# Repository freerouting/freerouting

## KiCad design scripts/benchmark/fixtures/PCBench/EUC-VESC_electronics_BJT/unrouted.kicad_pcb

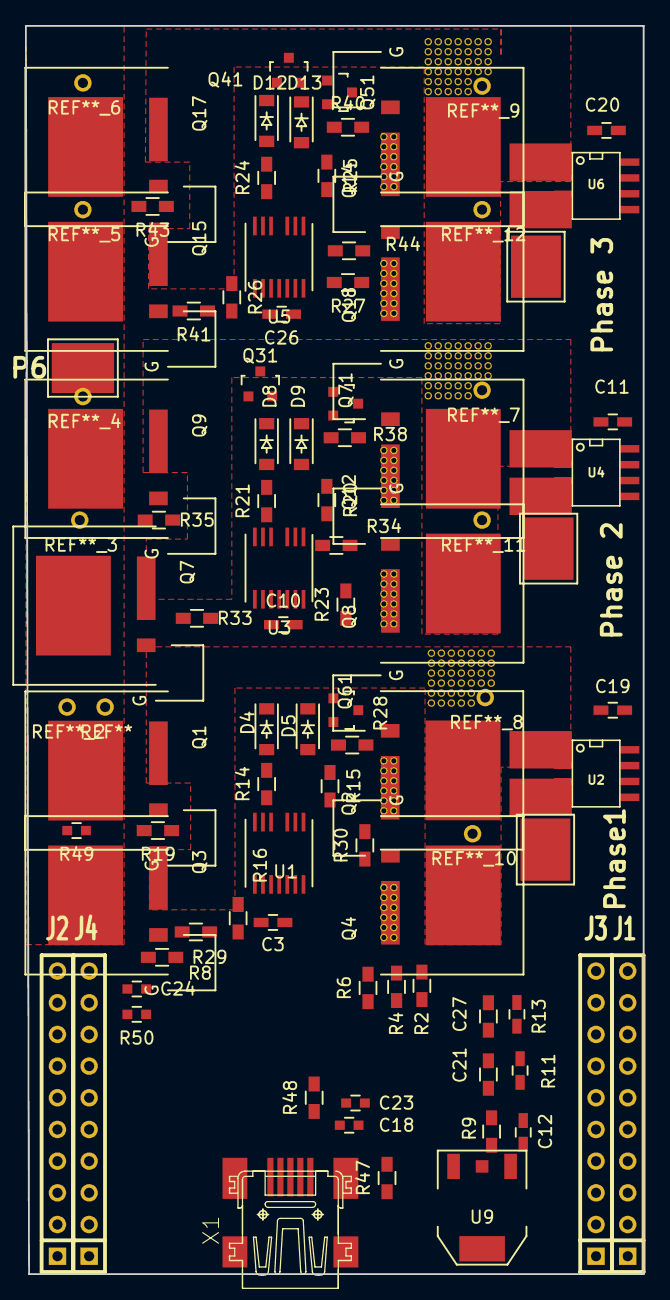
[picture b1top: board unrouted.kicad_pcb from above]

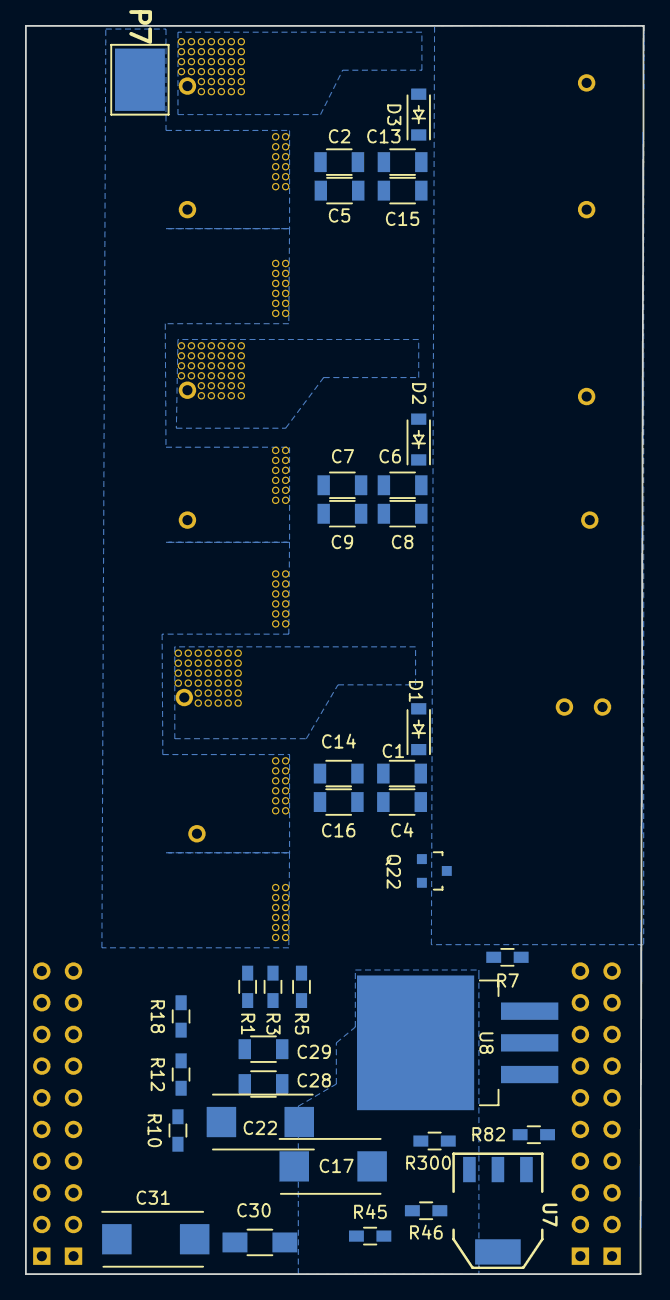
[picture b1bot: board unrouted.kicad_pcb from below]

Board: 4 copper layers, 49.5 x 100.1 mm, 120 parts (36 on the bottom side), 68 nets, no tracks yet.

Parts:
C1, C2, C6, C7, C13, C14: 0.1uf; C_1206
C3, C10, C11, C12, C19, C20, C21, C26, C27: 0.1uf; C_0603_HandSoldering
C4, C5, C8, C9, C15, C16, C28, C29: 10uf; C_1206
C17, C22, C31: 100uf; TantalC_SizeD_EIA-7343_Reflow
C18, C23, C24: 10uf; C_0603
C30: 2.2uf; C_1206_HandSoldering
D1, D2, D3: DFLS1150-7; SOD-123
D4, D5, D8, D9, D12, D13: D_Schottky_Small; SOD-123
J1: Ti_Booster_40_J1; SIL-10J1
J2: Ti_Booster_40_J2; SIL-10J2
J3: Ti_Booster_40_J3; SIL-10J3
J4: Ti_Booster_40_J4; SIL-10J4
P6: IN+; 1PAD_4x5mm
P7: IN-; 1PAD_4x5mm
Phase1: MOTOR3; 1PAD_4x5mm
Phase 2: MOTOR2; 1PAD_4x5mm
Phase 3: MOTOR1; 1PAD_4x5mm
Q1, Q2, Q3, Q4, Q7, Q8, Q9, Q12, Q14, Q15, Q17, Q18: FDMT-800; PQFN-8L-FET
Q22, Q31, Q41, Q51, Q61, Q71: BC807-40; SOT-23
R1, R3, R5, R7: 1.3K; R_0603_HandSoldering
R2, R4, R6, R8: 39K; R_0603_HandSoldering
R9, R11, R13: 2k; R_0603_HandSoldering
R10, R12, R18: 3.9k; R_0603_HandSoldering
R14, R15, R20, R21, R24, R25: 10R; R_0603_HandSoldering
R16, R23, R26, R27: 39k; R_0603_HandSoldering
R19, R28, R29, R30, R33, R34, R35, R38, R40, R41, R43, R44, R45, R46: R22; R_0603_HandSoldering
R47: R0; R_0603_HandSoldering
R48: r0; R_0603_HandSoldering
R49: NTC10K; C_0603
R50: 10K; C_0603
R82: R; R_0603_HandSoldering
R300: R_Small; R_0603_HandSoldering
U1, U3, U5: ADuM7223; LGA-13
U2, U4, U6: ACS723; ACS723_40
U7: NCP1117ST33T3G; SOT-223
U8: tl783; TO-263-3Lead
U9: LM340MPX-5; SOT-223
X1: MINI-USB-SCHIELD-32005-201; con-cypressindustries-32005-201

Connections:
+3V3: C30.1, C31.1, J1.1, R49.1, U7.2
+5V: C3.2, C10.2, C11.1, C17.1, C18.1, C19.2, C20.1, C23.1, C26.1, J3.1, R47.2, U1.7, U2.8, U3.7, U4.8, U5.7, U6.8, U7.3, U9.3
/Power MOSFETS/CurrentA: C12.1, J3.7, R9.2, R10.1
/Power MOSFETS/CurrentB: C21.1, J3.8, R11.2, R12.1
/Power MOSFETS/CurrentC: C27.1, J3.9, R13.2, R18.1
/Power MOSFETS/H1_VS: C1.2, C4.2, Q1.2, Q2.1, Q3.2, Q4.1, Q22.3, R2.2, R16.1, U1.11, U2.1, U2.2
/Power MOSFETS/H2_VS: C6.2, C8.2, Q7.2, Q8.1, Q9.2, Q12.1, Q31.3, R4.2, U3.11, U4.1, U4.2
/Power MOSFETS/H3_VS: C13.2, C15.2, Q14.1, Q15.2, Q17.2, Q18.1, Q41.3, R6.2, R26.1, U5.11, U6.1, U6.2
/Power MOSFETS/M_H1: J4.1, U1.2
/Power MOSFETS/M_H2: J4.3, U3.2
/Power MOSFETS/M_H3: J4.5, U5.2
/Power MOSFETS/M_L1: J4.2, U1.3
/Power MOSFETS/M_L2: J4.4, U3.3
/Power MOSFETS/M_L3: J4.6, U5.3
/Power MOSFETS/PHASE_1: Phase1.1, U2.3, U2.4
/Power MOSFETS/PHASE_2: Phase 2.1, U4.3, U4.4
/Power MOSFETS/PHASE_3: Phase 3.1, U6.3, U6.4
GND: C2.2, C3.1, C5.2, C7.2, C9.2, C10.1, C11.2, C12.2, C14.2, C16.2, C17.2, C18.2, C19.1, C20.2, C21.2, C22.2, C23.2, C24.1, C26.2, C27.2, C28.1, C29.1, C30.2, C31.2, J2.1, J3.2, P7.1, Q2.2, Q4.2, Q8.2, Q12.2, Q14.2, Q18.2, Q51.3, Q61.3, Q71.3, R1.1, R3.1, R5.1, R7.1, R10.2, R12.2, R18.2, R23.1, R27.1, R48.1, R50.1, R300.2, U1.1, U1.5, U1.8, U2.5, U3.1, U3.5, U3.8, U4.5, U5.1, U5.5, U5.8, U6.5, U7.1, U9.2, U9.4
unnamed: C1.1, C4.1, D1.1, U1.13
unnamed: C6.1, C8.1, D2.1, U3.13
unnamed: C13.1, C15.1, D3.1, U5.13
unnamed: C24.2, J2.10, R49.2, R50.2
unnamed: D4.1, Q22.2, R16.2, R19.1, R29.1
unnamed: D4.2, Q22.1, R14.2
unnamed: D5.1, Q61.2, R28.2, R30.2
unnamed: D5.2, Q61.1, R15.1
unnamed: D8.1, Q31.2, R33.1, R35.1
unnamed: D8.2, Q31.1, R21.2
unnamed: D9.1, Q71.2, R34.1, R38.1
unnamed: D9.2, Q71.1, R20.1
unnamed: D12.1, Q41.2, R26.2, R41.1, R43.1
unnamed: D12.2, Q41.1, R24.2
unnamed: D13.1, Q51.2, R40.1, R44.1
unnamed: D13.2, Q51.1, R25.1
unnamed: J2.2, J2.3, R45.2
unnamed: J2.4, J2.5, R46.1
unnamed: J3.3, R7.2, R8.1
unnamed: J3.4, R1.2, R2.1
unnamed: J3.5, R3.2, R4.1
unnamed: J3.6, R5.2, R6.1
unnamed: Q1.3, R19.2
unnamed: Q2.3, R28.1
unnamed: Q3.3, R29.2
unnamed: Q4.3, R30.1
unnamed: Q7.3, R33.2
unnamed: Q8.3, R34.2
unnamed: Q9.3, R35.2
unnamed: Q12.3, R38.2
unnamed: Q14.3, R40.2
unnamed: Q15.3, R41.2
unnamed: Q17.3, R43.2
unnamed: Q18.3, R44.2
unnamed: R9.1, U2.7
unnamed: R11.1, U4.7
unnamed: R13.1, U6.7
unnamed: R14.1, U1.12
unnamed: R15.2, U1.9
unnamed: R20.2, U3.9
unnamed: R21.1, U3.12
unnamed: R24.1, U5.12
unnamed: R25.2, U5.9
unnamed: R45.1, X1.3
unnamed: R46.2, X1.2
unnamed: R47.1, X1.5
unnamed: R48.2, X1.1
unnamed: R82.2, R300.1, U8.1
VDD: C2.1, C5.1, C7.1, C9.1, C14.1, C16.1, C22.1, C28.2, C29.2, D1.2, D2.2, D3.2, R82.1, U3.10, U5.10, U8.2, U8.4, U9.1
V_SUPPLY: P6.1, Q1.1, Q3.1, Q7.1, Q9.1, Q15.1, Q17.1, R8.2, U8.3

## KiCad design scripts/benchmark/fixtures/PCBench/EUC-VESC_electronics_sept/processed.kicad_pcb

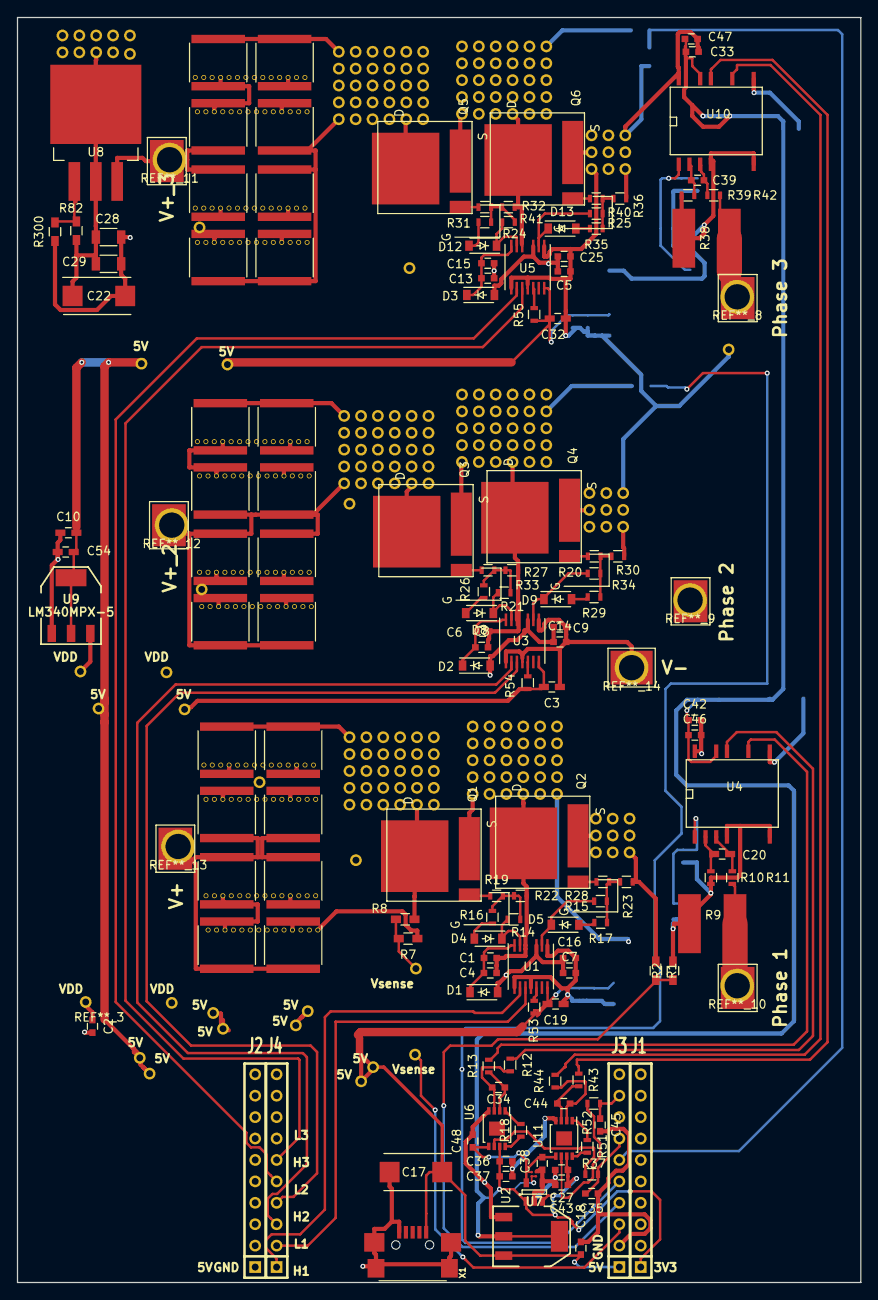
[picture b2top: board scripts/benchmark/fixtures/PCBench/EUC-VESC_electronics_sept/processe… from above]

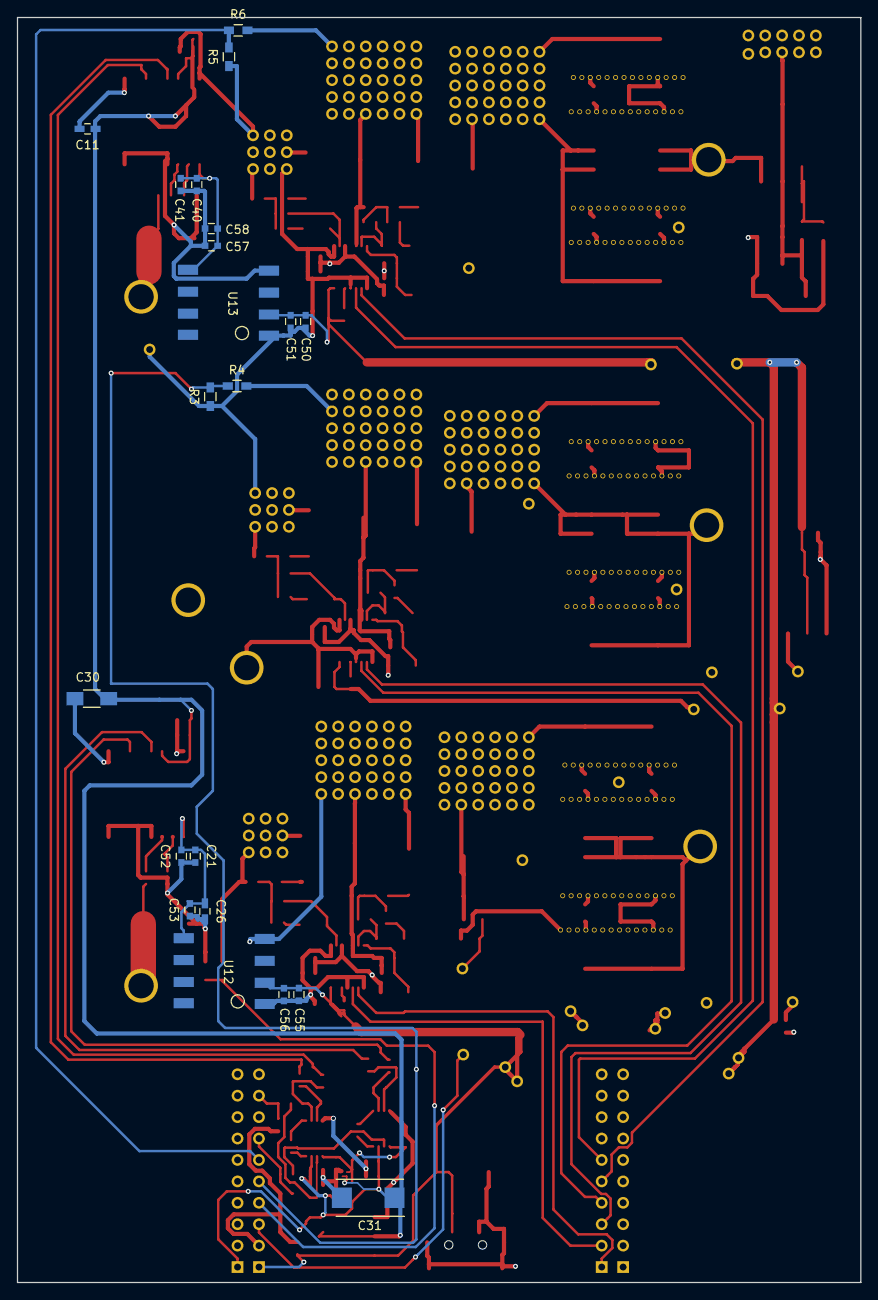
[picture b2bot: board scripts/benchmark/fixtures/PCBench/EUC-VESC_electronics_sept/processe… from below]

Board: 4 copper layers, 100.0 x 150.0 mm, 169 parts (21 on the bottom side), 74 nets.

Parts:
C1, C2, C6, C7, C13, C14, C25, C33, C36, C38, C41, C43, C46, C48, C50, C53, C55, C58: 0.1uf; C_0603
C3, C10, C19, C26, C32: 0.1uf; C_0603_HandSoldering
C4, C16: 2.2uf; C_0603
C5, C8, C9, C15: 2.2; C_0603
C11: 1uf; C_0603_HandSoldering
C17, C22, C31: 100uf; TantalC_SizeD_EIA-7343_Reflow
C18, C21, C27, C37, C40, C42, C47, C51, C52, C56, C57: 10uf; C_0603
C20: 33nf; C_0603_HandSoldering
C28, C29: 10uf; C_1206
C30: 2.2uf; C_1206_HandSoldering
C34, C44: 4.7nf; C_0603
C35, C45: 100pf; C_0603
C39: 33nf; C_0603
C49, C49_2, C49_3, C49_4, C49_5, C49_6, C49_7, C49_8, C49_9, C49_10, C49_11, C49_12, C49_13, C49_14, C49_15, C49_16, C49_17, C49_18, C49_19, C49_20, C49_21, C49_22, C49_23, C49_24: 15uf; C_2225_invis
C54: 10uf; C_0603_HandSoldering
D1, D2, D3: DFLS1150-7; SOD-123
D4, D5, D8, D9, D12, D13: D_Schottky_Small; SOD-123
J1: Ti_Booster_40_J1; SIL-10J1
J2: Ti_Booster_40_J2; SIL-10J2
J3: Ti_Booster_40_J3; SIL-10J3
J4: Ti_Booster_40_J4; SIL-10J4
Phase 1: MOTOR3; 1PAD_4x5mm
Phase 2: MOTOR2; 1PAD_4x5mm
Phase 3: MOTOR1; 1PAD_4x5mm
Q1, Q2, Q3, Q4, Q5, Q6: FDMT-800; P-PG-HSOF-08
R1, R3, R5, R7: 1.3K; R_0603_HandSoldering
R2, R4, R6, R8: 39K; R_0603_HandSoldering
R9, R38: 0.001R; shunt_ERJ-MS6SF1M0U
R10, R11, R37, R39, R42, R52: 20R; R_0603
R12, R13, R43, R44: R20; R_0603
R14, R15, R20, R21, R24, R25: 10R; R_0603
R16, R17, R26, R29, R31, R35: R4; R_0603
R18, R51: 10Mr; R_0603
R19, R28, R33, R34, R40, R41: ferrite; R_0603
R22, R23, R27, R30, R32, R36: R39k; R_0603
R53, R54, R55: r20; R_0603
R82: R; R_0603_HandSoldering
R300: R_Small; R_0603_HandSoldering
U1, U3, U5: ADuM7223; LGA-13
U2: TPS72116DBVR; SOT-23-5
U4, U10: SI8920; SI_8920SO-16
U6, U11: ad623; MSOP-8-1EP_3x3mm_Pitch0.65mm
U7: NCP1117ST33T3G; SOT-223
U8: tl783; TO-263-3Lead
U9: LM340MPX-5; SOT223_bcp53
U12, U13: R1SE-0505-R; recom_power
V+: IN+; 1PAD_4x5mm
V+_2, V+_3: IN+; 1PAD_4x5mm
V-: IN-; 1PAD_4x5mm
X1: MINI-USB-SCHIELD-32005-201; USB-UX60R-MB-5ST

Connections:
+1V5: C38.1, C48.1, U2.5, U6.5, U11.5
+3V3: C11.1, C27.1, C30.1, C31.1, C33.1, C36.1, C37.1, C42.1, C43.1, C46.1, C47.1, J1.1, U2.1, U2.3, U4.8, U6.7, U7.2, U10.8, U11.7
+5V: C3.2, C10.2, C17.1, C18.1, C19.2, C32.1, C50.2, C51.2, C54.1, C55.2, C56.2, J3.1, R53.2, R54.2, R55.2, U1.7, U3.7, U5.7, U7.3, U9.3, U12.2, U13.2, X1.1
+5VA: C21.1, C26.1, C52.2, C53.2, U4.1, U12.5
+5VD: C40.1, C41.1, C57.2, C58.2, U10.1, U13.5
/Power MOSFETS/CurrentA: C35.1, J3.7, R37.1
/Power MOSFETS/CurrentC: C45.1, J3.9, R52.1
/Power MOSFETS/H2_VS: C6.2, C8.2, Phase 2.1, Q3.2, Q4.1, R4.2, R27.1, U3.11
/Power MOSFETS/M_H1: J4.1, U1.2
/Power MOSFETS/M_H2: J4.3, U3.2
/Power MOSFETS/M_H3: J4.5, U5.2
/Power MOSFETS/M_L1: J4.2, U1.3
/Power MOSFETS/M_L2: J4.4, U3.3
/Power MOSFETS/M_L3: J4.6, U5.3
/Power MOSFETS/PHASE_1: Phase 1.1, R9.1, R11.2
/Power MOSFETS/PHASE_3: Phase 3.1, R38.1, R42.2
/Power MOSFETS/sense1_N: R13.2, U4.6
/Power MOSFETS/sense1_P: R12.2, U4.7
/Power MOSFETS/sense2_N: R44.2, U10.6
/Power MOSFETS/sense2_P: R43.2, U10.7
GND: C2.2, C3.1, C5.2, C7.2, C9.2, C10.1, C11.2, C14.2, C16.2, C17.2, C18.2, C19.1, C22.2, C25.2, C27.2, C28.1, C29.1, C30.2, C31.2, C32.2, C33.2, C35.2, C36.2, C37.2, C38.2, C42.2, C43.2, C45.2, C46.2, C47.2, C48.2, C49.2, C49_2.2, C49_3.2, C49_4.2, C49_5.2, C49_6.2, C49_7.2, C49_8.2, C49_9.2, C49_10.2, C49_11.2, C49_12.2, C49_13.2, C49_14.2, C49_15.2, C49_16.2, C49_17.2, C49_18.2, C49_19.2, C49_20.2, C49_21.2, C49_22.2, C49_23.2, C49_24.2, C50.1, C51.1, C54.2, C55.1, C56.1, J2.1, J3.2, Q2.2, Q4.2, Q6.2, R1.1, R3.1, R5.1, R7.1, R23.1, R30.1, R36.1, R300.2, U1.1, U1.4, U1.8, U2.2, U2.4, U3.1, U3.4, U3.8, U4.5, U5.1, U5.4, U5.8, U6.4, U7.1, U9.2, U10.5, U11.4, U12.1, U13.1, V-.1, X1.5
GNDA: C1.2, C4.2, C21.2, C26.2, C52.1, C53.1, Q1.2, Q2.1, R2.2, R9.2, R10.2, R22.1, U1.11, U4.4, U12.4
GNDD: C13.2, C15.2, C40.2, C41.2, C57.1, C58.1, Q5.2, Q6.1, R6.2, R32.1, R38.2, R39.2, U5.11, U10.4, U13.4
unnamed: C1.1, C4.1, D1.1, U1.13
unnamed: C6.1, C8.1, D2.1, U3.13
unnamed: C13.1, C15.1, D3.1, U5.13
unnamed: C20.1, R10.1, U4.2
unnamed: C20.2, R11.1, U4.3
unnamed: C34.1, R12.1, U6.3
unnamed: C34.2, R13.1, U6.2
unnamed: C39.1, R39.1, U10.2
unnamed: C39.2, R42.1, U10.3
unnamed: C44.1, R43.1, U11.3
unnamed: C44.2, R44.1, U11.2
unnamed: D4.1, R14.2, U1.12
unnamed: D4.2, R16.2
unnamed: D5.1, R15.1, U1.9
unnamed: D5.2, R17.2
unnamed: D8.1, R21.1, U3.12
unnamed: D8.2, R26.2
unnamed: D9.1, R20.1, U3.9
unnamed: D9.2, R29.2
unnamed: D12.1, R24.1, U5.12
unnamed: D12.2, R31.2
unnamed: D13.1, R25.1, U5.9
unnamed: D13.2, R35.2
unnamed: J3.3, R7.2, R8.1
unnamed: J3.4, R1.2, R2.1
unnamed: J3.5, R3.2, R4.1
unnamed: J3.6, R5.2, R6.1
unnamed: Q1.3, R19.1
unnamed: Q2.3, R28.2
unnamed: Q3.3, R33.1
unnamed: Q4.3, R34.1
unnamed: Q5.3, R41.1
unnamed: Q6.3, R40.1
unnamed: R14.1, R16.1, R19.2, R22.2
unnamed: R15.2, R17.1, R23.2, R28.1
unnamed: R18.1, U6.8
unnamed: R18.2, U6.1
unnamed: R20.2, R29.1, R30.2, R34.2
unnamed: R21.2, R26.1, R27.2, R33.2
unnamed: R24.2, R31.1, R32.2, R41.2
unnamed: R25.2, R35.1, R36.2, R40.2
unnamed: R37.2, U6.6
unnamed: R51.1, U11.8
unnamed: R51.2, U11.1
unnamed: R52.2, U11.6
unnamed: R53.1, U1.5
unnamed: R54.1, U3.5
unnamed: R55.1, U5.5
unnamed: R82.2, R300.1, U8.1
VDD: C2.1, C5.1, C7.1, C9.1, C14.1, C16.1, C22.1, C25.1, C28.2, C29.2, D1.2, D2.2, D3.2, R82.1, U1.10, U3.10, U5.10, U8.2, U8.4, U9.1
V_SUPPLY: C49.1, C49_2.1, C49_3.1, C49_4.1, C49_5.1, C49_6.1, C49_7.1, C49_8.1, C49_9.1, C49_10.1, C49_11.1, C49_12.1, C49_13.1, C49_14.1, C49_15.1, C49_16.1, C49_17.1, C49_18.1, C49_19.1, C49_20.1, C49_21.1, C49_22.1, C49_23.1, C49_24.1, Q1.1, Q3.1, Q5.1, R8.2, U8.3, V+.1, V+_2.1, V+_3.1

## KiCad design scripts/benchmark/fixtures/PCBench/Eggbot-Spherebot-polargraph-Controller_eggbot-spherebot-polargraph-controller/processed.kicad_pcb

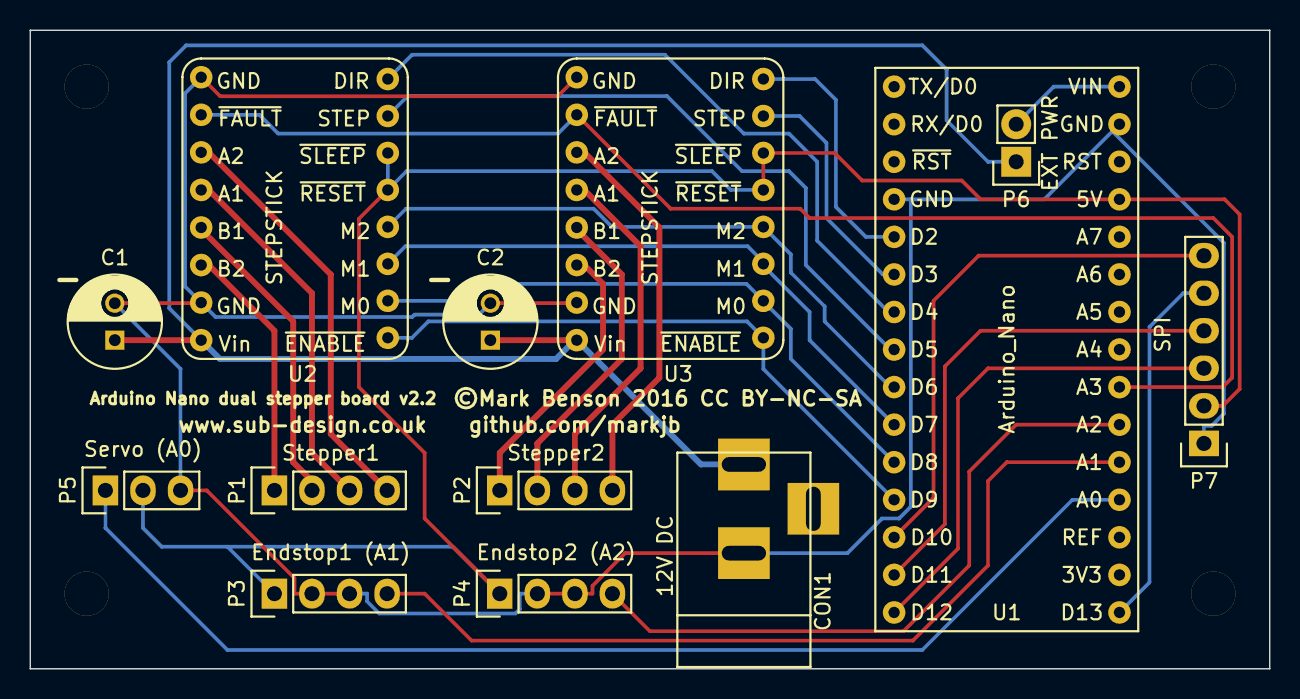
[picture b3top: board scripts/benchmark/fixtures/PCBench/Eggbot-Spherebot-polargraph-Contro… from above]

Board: 2 copper layers, 83.8 x 43.2 mm, 13 parts (0 on the bottom side), 28 nets.

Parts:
C1, C2: CP; C_Radial_D6.3_L11.2_P2.5
CON1: 12V DC; BARREL_JACK
P1: Stepper1; Pin_Header_Straight_1x04
P2: Stepper2; Pin_Header_Straight_1x04
P3: Endstop1 (A1); Pin_Header_Straight_1x04
P4: Endstop2 (A2); Pin_Header_Straight_1x04
P5: Servo (A0); Pin_Header_Straight_1x03
P6: EXT PWR; Pin_Header_Straight_1x02
P7: SPI; Pin_Header_Straight_1x06
U1: Arduino_Nano; Arduino_nano_v3
U2, U3: STEPSTICK; Stepstick

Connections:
+12V: C1.1, C2.1, CON1.1, P6.1, U2.8, U3.8
/DIR1: U1.7, U2.16
/DIR2: U1.5, U3.16
/ENABLE: U1.12, U2.9, U3.9
/ESTOP1: P3.4, U1.20
/ESTOP2: P4.4, U1.21
/FAULT: U1.22, U2.2, U3.2
/M0: U1.11, U2.10, U3.10
/M1: U1.10, U2.11, U3.11
/M2: U1.9, U2.12, U3.12
/MISO: P7.3, U1.15
/MOSI: P7.4, U1.14
/SCK: P7.5, U1.16
/SD_SEL: P7.6, U1.13
/SERVO: P5.1, U1.19
/STEP1: U1.8, U2.15
/STEP2: U1.6, U3.15
/VCC: P3.1, P4.1, P5.2, P7.2, U1.27, U2.13, U2.14, U3.13, U3.14
GND: C1.2, C2.2, CON1.2, P3.2, P3.3, P4.2, P4.3, P5.3, P7.1, U1.4, U1.29, U2.1, U2.7, U3.1, U3.7
unnamed: P1.1, U2.6
unnamed: P1.2, U2.5
unnamed: P1.3, U2.4
unnamed: P1.4, U2.3
unnamed: P2.1, U3.6
unnamed: P2.2, U3.5
unnamed: P2.3, U3.4
unnamed: P2.4, U3.3
unnamed: P6.2, U1.30

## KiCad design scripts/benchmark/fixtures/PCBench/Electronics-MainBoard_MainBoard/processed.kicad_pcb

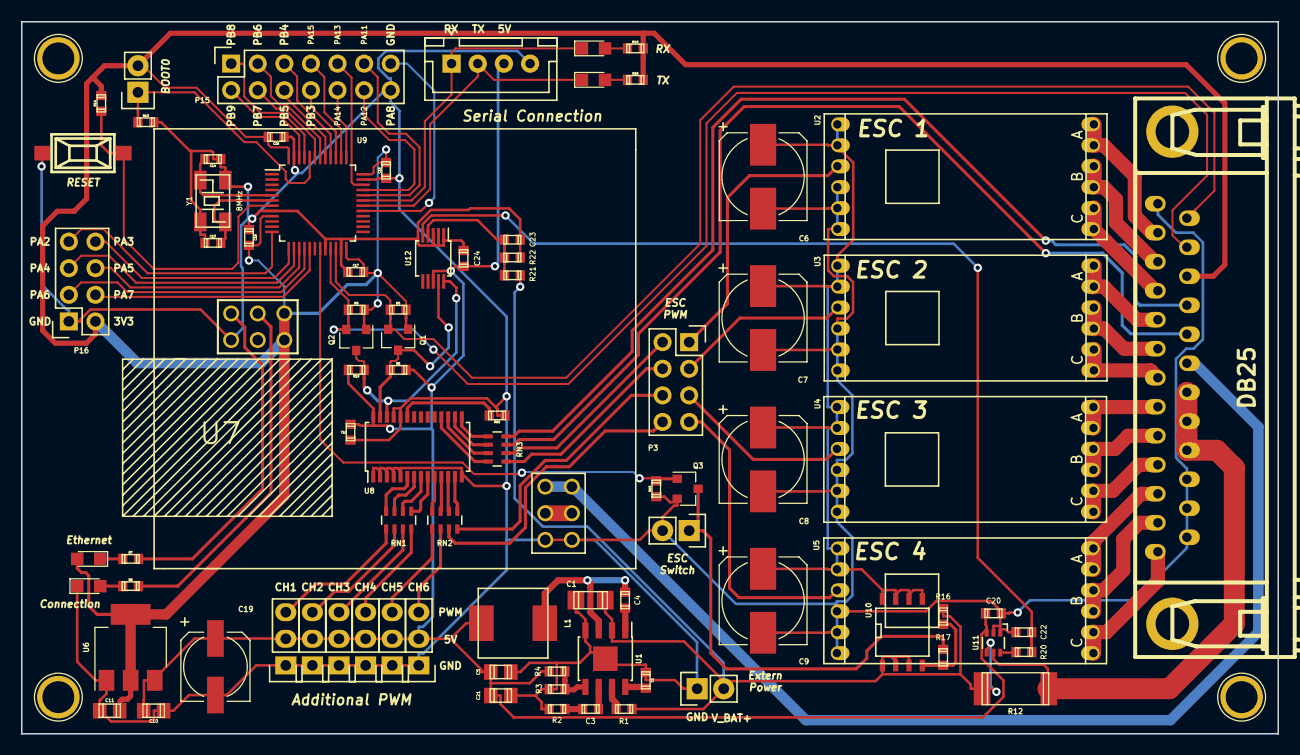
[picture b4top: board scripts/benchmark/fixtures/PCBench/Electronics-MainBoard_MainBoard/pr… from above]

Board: 2 copper layers, 120.0 x 68.0 mm, 89 parts (0 on the bottom side), 96 nets.

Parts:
C1: 10uF/25V; c_1206
C2, C20, C23, C24: 0.1uF; c_0603
C3: 3.9nF; c_0603
C4: 10nF; c_0603
C5, C21: 22uF/10V; c_0805
C6, C7, C8, C9: 220uF/25V; CP_Elec_8x10
C10, C11: 1uF; c_0805
C12: 10uF; c_0603
C13, C14: 33pF; c_0603
C15, C16, C17, C18, C22: 1uF; c_0603
C19: 220uF/10V; CP_Elec_6.3x5.8
D1, D2, D3, D4: LED; LED_0805
J1: DB25; DB_25M
L1: 10uH/4A; ASPI-0630LR
P1: BOOT; Socket_Strip_Straight_1x02
P2: CONN_01X04; JST_XH_B04B-XH-A_04x2.50mm_Straight
P3, P16: CONN_02X04; Socket_Strip_Straight_2x04
P4, P5, P6, P7: HOLE; 1pin
P8, P14: CONN_01X02; Socket_Strip_Straight_1x02
P9, P10, P11, P12, P13, P18: CONN_01X03; Socket_Strip_Straight_1x03
P15: CONN_02X07; Socket_Strip_Straight_2x07
Q1, Q2: BSS138; SOT-23
Q3: DMN65D8L; SOT-23
R1: 100k; r_0603
R2: 6.8k; r_0603
R3: 10k 1%; r_0603
R4: 44.2k 1%; r_0603
R5, R8, R9, R10, R11, R13, R14, R15, R16: 10k; r_0603
R6, R7, R18, R19: 330; r_0603
R12: 0.003 %1; r_2512
R17: 1k; r_0603
R20: 3.3k; r_0603
R21: 30.1k %1; r_0603
R22: 10k %1; r_0603
RN1, RN2, RN3: 20k; R_Array_Concave_4x0603
SW1: RESET; smd_push
U1: mp2307; SOIC-8-1EP_3.9x4.9mm_Pitch1.27mm
U2, U3, U4, U5: DYS_mini_ESC; DYS_Mini_ESC
U6: TLV1117LV33; SOT-223
U7: TENDA_P200; Tenda_p200
U8: pca9685; TSSOP-28_4.4x9.7mm_Pitch0.65mm
U9: STM32F103CBT6; LQFP-48_7x7mm_Pitch0.5mm
U10: SI4425DDY; SOIC-8-N
U11: INA199A2; SC-70-6
U12: ADS1015; MSOP-10_3x3mm_Pitch0.5mm
Y1: 8MHz; crystal_maple

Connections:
/3V3: C11.1, C15.1, C16.1, C17.1, C18.1, D2.2, J1.23, P1.2, P16.2, Q1.1, Q2.1, R5.1, R9.1, R14.1, R18.1, R19.1, U6.2, U6.4, U7.3V3, U9.9, U9.24, U9.36, U9.48
/5V: C5.1, C10.1, C12.1, C19.1, C20.1, C21.1, C24.1, L1.2, P2.3, P9.2, P10.2, P11.2, P12.2, P13.2, P18.2, R4.1, R8.1, R10.1, U6.3, U8.28, U11.3, U12.8
/ADC_I: C22.1, R20.1, U12.5
/ADC_V: C23.1, R21.2, R22.1, U12.4
/CH0: P9.3, RN1.1
/CH1: P10.3, RN1.2
/CH2: P11.3, RN1.3
/CH3: P12.3, RN1.4
/CH4: P13.3, RN2.1
/CH5: P18.3, RN2.2
/CH6: P3.8, RN2.3
/CH7: P3.6, RN2.4
/CH10: P3.2, RN3.6
/CH11: P3.4, RN3.5
/ESC1: P3.1, U2.2
/ESC2: P3.3, U3.2
/ESC3: P3.5, U4.2
/ESC4: P3.7, U5.2
/LED1: J1.21, RN3.7
/LED2: J1.22, RN3.8
/MOTOR_1A: J1.12, U2.4
/MOTOR_1B: J1.11, U2.5
/MOTOR_1C: J1.10, U2.6
/MOTOR_2A: J1.9, U3.4
/MOTOR_2B: J1.8, U3.5
/MOTOR_2C: J1.7, U3.6
/MOTOR_3A: J1.6, U4.4
/MOTOR_3B: J1.5, U4.5
/MOTOR_3C: J1.4, U4.6
/MOTOR_4A: J1.3, U5.4
/MOTOR_4B: J1.2, U5.5
/MOTOR_4C: J1.1, U5.6
/OSC_N: C14.1, U9.5, Y1.2
/OSC_P: C13.1, U9.6, Y1.1
/PA2: P16.7, U9.12
/PA3: P16.8, U9.13
/PA4: P16.5, U9.14
/PA5: P16.6, U9.15
/PA6: P16.3, U9.16
/PA7: P16.4, U9.17
/PA8: P15.13, U9.29
/PA11: P15.11, U9.32
/PA12: P15.12, U9.33
/PA13: P15.9, U9.34
/PA14: P15.10, U9.37
/PA15: P15.7, U9.38
/PB3: P15.8, U9.39
/PB4: P15.5, U9.40
/PB5: P15.6, U9.41
/PB6: P15.3, U9.42
/PB7: P15.4, U9.43
/PB8: P15.1, U9.45
/PB9: P15.2, U9.46
/PWR_SW: Q3.1, R15.1, U9.19
/RX1: D4.1, P2.1, U9.31
/SCL_3V3: J1.24, Q2.2, R9.2, U9.21
/SCL_5V: Q2.3, R10.2, U8.26, U12.10
/SDA_3V3: J1.25, Q1.2, R5.2, U9.22
/SDA_5V: Q1.3, R8.2, U8.27, U12.9
/T+: J1.20, U7.T_+
/TX1: D3.1, P2.2, U9.30
/V_BAT: C1.1, P8.2, R1.1, R12.1, R16.1, R21.1, U1.2, U10.1, U10.2, U10.3, U11.4
/V_IN: J1.17, J1.18, J1.19, R12.2, U11.5
/V_PWR: C6.1, C7.1, C8.1, C9.1, U2.3, U3.3, U4.3, U5.3, U10.5, U10.6, U10.7, U10.8
GND: C1.2, C2.2, C5.2, C6.2, C7.2, C8.2, C9.2, C10.2, C11.2, C12.2, C13.2, C14.2, C15.2, C16.2, C17.2, C18.2, C19.2, C20.2, C21.2, C22.2, C23.2, C24.2, D1.1, J1.13, J1.14, J1.15, J1.16, P2.4, P8.1, P9.1, P10.1, P11.1, P12.1, P13.1, P14.2, P15.14, P16.1, P18.1, Q3.2, R2.2, R3.2, R11.2, R13.1, R15.2, R22.2, SW1.1, U1.4, U1.9, U2.1, U3.1, U4.1, U5.1, U6.1, U7.GND, U7.T_-, U8.1, U8.2, U8.3, U8.4, U8.5, U8.14, U8.24, U8.25, U9.8, U9.20, U9.23, U9.35, U9.47, U11.1, U11.2, U12.1, U12.2, U12.3, Y1.3
unnamed: C2.1, U1.8
unnamed: C3.1, U1.6
unnamed: C3.2, R2.1
unnamed: C4.1, L1.1, U1.3
unnamed: C4.2, U1.1
unnamed: D1.2, R6.2
unnamed: D2.1, R7.2
unnamed: D3.2, R18.2
unnamed: D4.2, R19.2
unnamed: P1.1, R13.2, U9.44
unnamed: P14.1, Q3.3, R17.2
unnamed: R1.2, U1.7
unnamed: R3.1, R4.2, U1.5
unnamed: R6.1, U7.C
unnamed: R7.1, U7.E
unnamed: R11.1, U8.23
unnamed: R14.2, SW1.2, U9.7
unnamed: R16.2, R17.1, U10.4
unnamed: R20.2, U11.6
unnamed: RN1.5, U8.9
unnamed: RN1.6, U8.8
unnamed: RN1.7, U8.7
unnamed: RN1.8, U8.6
unnamed: RN2.5, U8.13
unnamed: RN2.6, U8.12
unnamed: RN2.7, U8.11
unnamed: RN2.8, U8.10
unnamed: RN3.1, U8.15
unnamed: RN3.2, U8.16
unnamed: RN3.3, U8.17
unnamed: RN3.4, U8.18

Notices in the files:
scripts/benchmark/fixtures/PCBench/Eggbot-Spherebot-polargraph-Controller_eggbot-spherebot-polargraph-controller/processed.kicad_pcb:
©Mark Benson 2016 CC BY-NC-SA
